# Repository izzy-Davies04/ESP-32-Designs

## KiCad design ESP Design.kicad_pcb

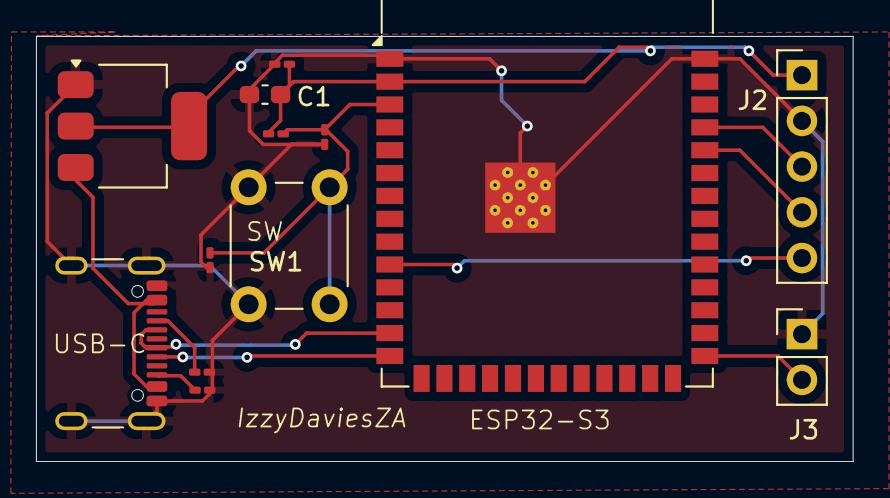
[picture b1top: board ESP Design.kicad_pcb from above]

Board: 2 copper layers, 45.4 x 23.6 mm, 13 parts (0 on the bottom side), 12 nets.

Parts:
C1: 22uF; C_0603_1608Metric_Pad1.08x0.95mm_HandSolder
C2, C3, C4: 0.1uF; C_0201_0603Metric_Pad0.64x0.40mm_HandSolder
J1: USB_C_Receptacle_USB2.0_16P; USB_C_Receptacle_GCT_USB4105-xx-A_16P_TopMnt_Horizontal
J2: Conn_01x05; PinHeader_1x05_P2.54mm_Vertical
J3: Conn_01x02_Pin; PinHeader_1x02_P2.54mm_Vertical
R1: 10k; R_0201_0603Metric_Pad0.64x0.40mm_HandSolder
R2, R3: 5.1k; R_0201_0603Metric_Pad0.64x0.40mm_HandSolder
SW1: SW_MEC_5E; SW_PUSH_6mm
U1: ESP32-S3-WROOM-1
U2: TLV76133DCY; SOT-223-3_TabPin2

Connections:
/3p3V: C1.1, C2.1, J2.1, R1.1, U1.2 (3V3), U2.2 (VO)
/IO0: J3.2, U1.27 (IO0)
/IO17: J2.5, U1.10 (IO17)
/RXD: J2.4, U1.36 (RXD0)
/TXD: J2.3, U1.37 (TXD0)
/USB-Dm: J1.A7 (D-), J1.B7 (D-), U1.13 (USB_D-)
/USB-Dp: J1.A6 (D+), J1.B6 (D+), U1.14 (USB_D+)
GND: C1.2, C2.2, C3.2, C4.1, J1.A1 (GND), J1.A12 (GND), J1.B1 (GND), J1.B12 (GND), J1.S1 (SHIELD), J2.2, J3.1, R2.2, R3.2, SW1.1, U1.1 (GND), U1.40 (GND), U1.41 (GND), U2.1 (GND)
unnamed: J1.A5 (CC1), R3.1
unnamed: J1.B5 (CC2), R2.1
unnamed: C3.1, C4.2, R1.2, SW1.2, U1.3 (EN)
unnamed: J1.A4 (VBUS), J1.A9 (VBUS), J1.B4 (VBUS), J1.B9 (VBUS), U2.3 (VI)
